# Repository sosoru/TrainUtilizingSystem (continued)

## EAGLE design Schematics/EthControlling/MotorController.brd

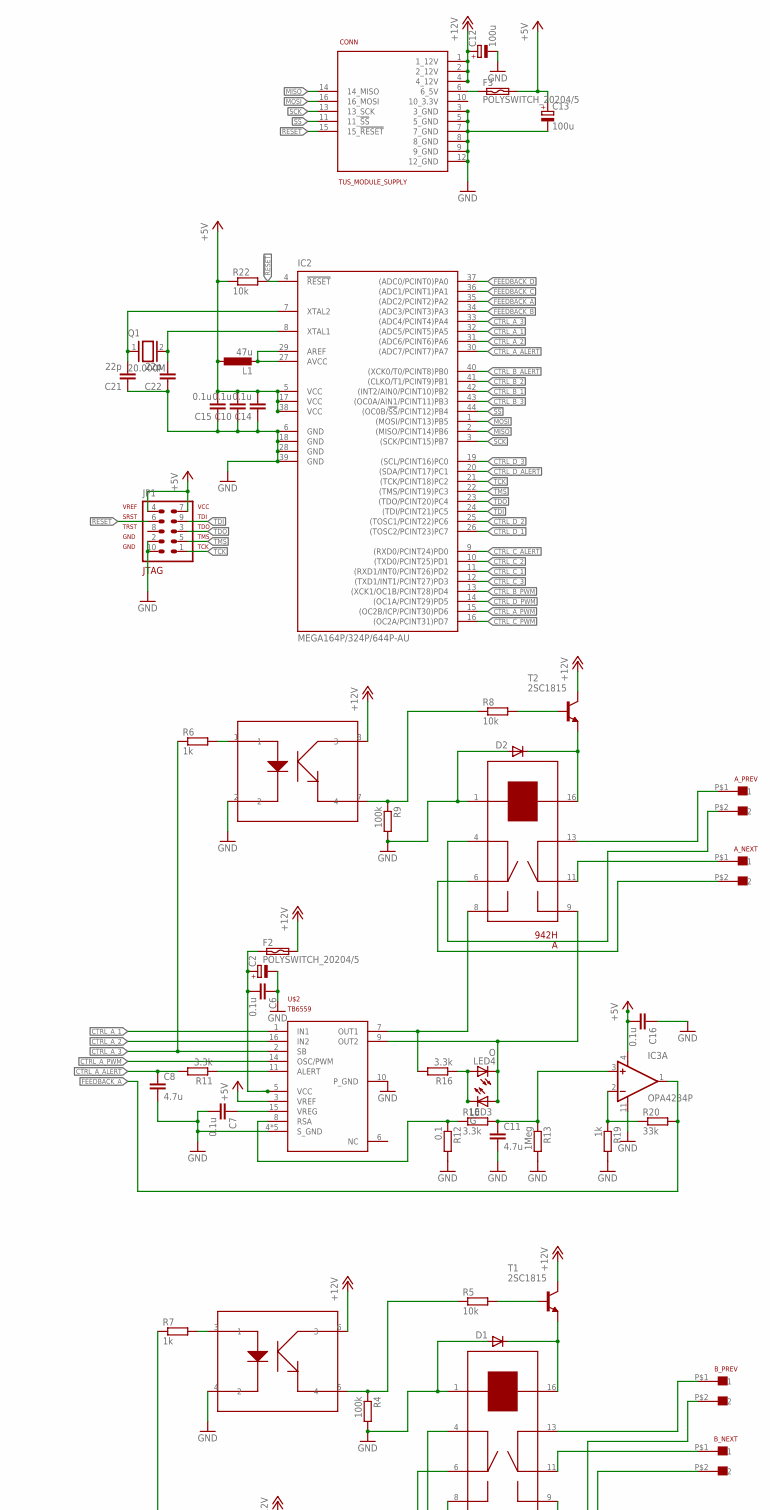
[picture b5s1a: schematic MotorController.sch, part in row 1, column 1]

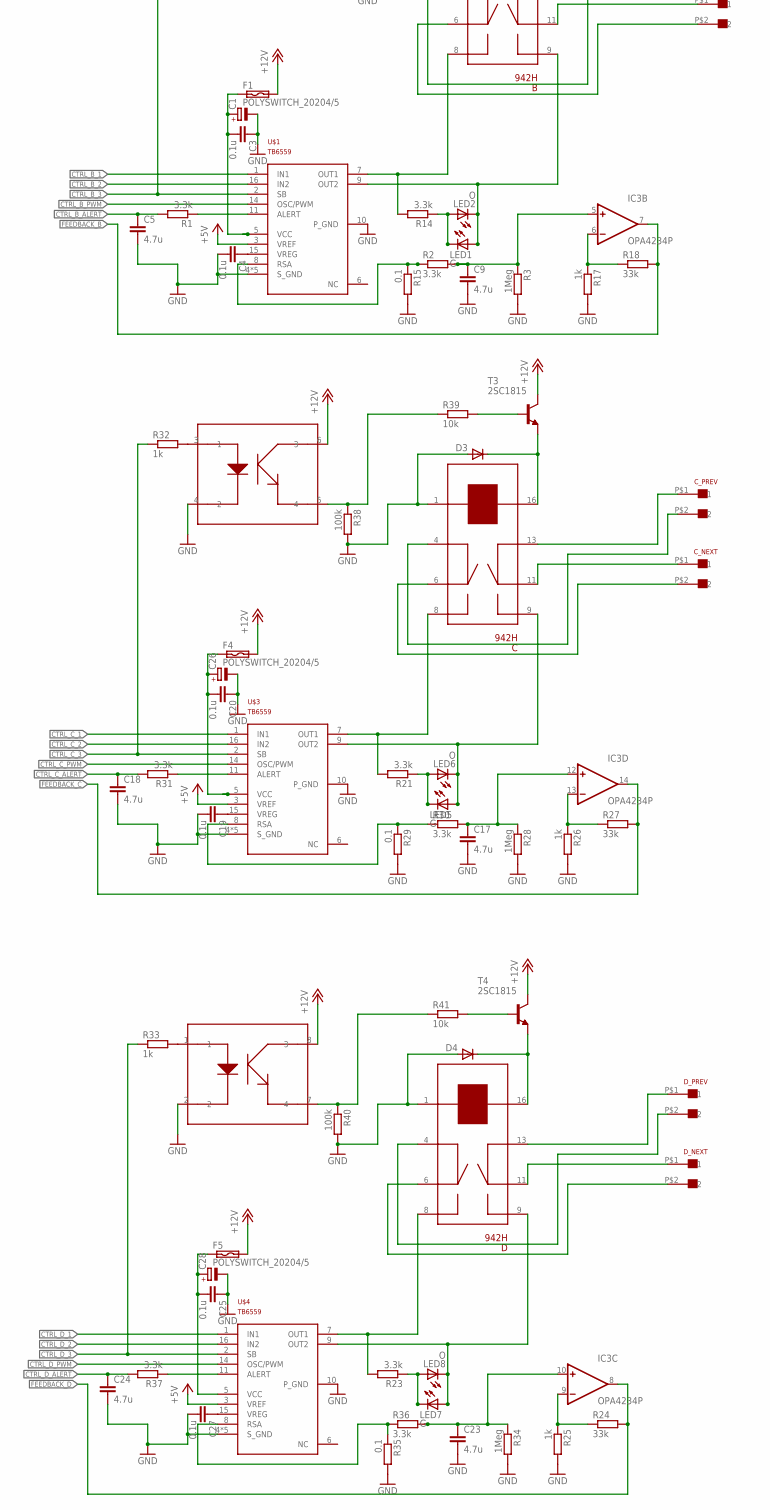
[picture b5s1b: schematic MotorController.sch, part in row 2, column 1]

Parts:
A: 942H; 941H-2C-12D
A_NEXT: XH-2
A_PREV: XH-2
B: 942H; 941H-2C-12D
B_NEXT: XH-2
B_PREV: XH-2
C: 942H; 941H-2C-12D
C1, C2, C26, C28: CPOL-EUE2,5-6E; E2,5-6E
C3, C4, C6, C7, C10, C14, C15, C16, C19, C20, C25, C27: 0.1u; C0603
C5, C8, C9, C11, C17, C18, C23, C24: 4.7u; C0603
C12: 100u; E2,5-6
C13: 100u; E2-5
C21, C22: 22p; C0603
CONN: TUS_MODULE_SUPPLY; 2X08
C_NEXT: XH-2
C_PREV: XH-2
D: 942H; 941H-2C-12D
D1, D2, D3, D4: 1N4148DO35-7; DO35-7
D_NEXT: XH-2
D_PREV: XH-2
F1, F2, F3, F4, F5: POLYSWITCH_20204/5; 0204/5
IC1, IC4: TLP621-2; SOCKET-08
IC2: MEGA164P/324P/644P-AU; TQFP44
IC3: OPA4234P; DIL14
JP1: AVR-JTAG-10
L1: 47u; L3216C
LED1, LED3, LED5, LED7: G; LED3MM
LED2, LED4, LED6, LED8: O; LED3MM
Q1: 20.000M; QS
R1, R2, R10, R11, R14, R16, R21, R23, R30, R31, R36, R37: 3.3k; R0603
R3, R13, R28, R34: 1Meg; R0603
R4, R9, R38, R40: 100k; R0603
R5, R8, R22, R39, R41: 10k; R0603
R6, R7, R17, R19, R25, R26, R32, R33: 1k; R0603
R12, R15, R29, R35: 0.1; R1206
R18, R20, R24, R27: 33k; R0603
T1, T2, T3, T4: 2SC1815; TO92-ECB
U$1, U$2, U$3, U$4: TB6559; HSOP-16

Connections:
!RESET: CONN.15 (15_!RESET), IC2.4 (!RESET), JP1.6, R22.2
!SS: CONN.11 (11_!SS), IC2.44 ((OC0B/!SS!/PCINT12)PB4)
+5V: C10.2, C13.+, C14.2, C15.2, C16.2, F3.2, IC2.5 (VCC), IC2.17 (VCC), IC2.38 (VCC), IC3.4 (V+), JP1.4, JP1.7, L1.1, R22.1, U$1.3 (VREF), U$2.3 (VREF), U$3.3 (VREF), U$4.3 (VREF)
+12V: C12.+, CONN.1 (1_12V), CONN.2 (2_12V), CONN.4 (4_12V), F1.2, F2.2, F4.2, F5.2, IC1.6 (3), IC1.8 (3), IC4.6 (3), IC4.8 (3), T1.C, T2.C, T3.C, T4.C
A_OUT1: A.8 (1), R16.2, U$2.7 (OUT1)
A_OUT2: A.9 ('1), LED3.A, LED4.K (C), U$2.9 (OUT2)
A_OUT3: C.8 (1), R21.2, U$3.7 (OUT1)
A_OUT4: C.9 ('1), LED5.A, LED6.K (C), U$3.9 (OUT2)
A_OUT5: B.8 (1), R14.2, U$1.7 (OUT1)
A_OUT6: B.9 ('1), LED1.A, LED2.K (C), U$1.9 (OUT2)
A_OUT7: D.8 (1), R23.2, U$4.7 (OUT1)
A_OUT8: D.9 ('1), LED7.A, LED8.K (C), U$4.9 (OUT2)
CTRL_A_1: IC2.32 ((ADC5/PCINT5)PA5), U$2.1 (IN1)
CTRL_A_2: IC2.31 ((ADC6/PCINT6)PA6), U$2.16 (IN2)
CTRL_A_3: IC2.33 ((ADC4/PCINT4)PA4), R6.1, U$2.2 (SB)
CTRL_A_ALERT: C8.1, IC2.30 ((ADC7/PCINT7)PA7), R11.2
CTRL_A_PWM: IC2.15 ((OC2B/ICP/PCINT30)PD6), U$2.14 (OSC/PWM)
CTRL_B_1: IC2.42 ((INT2/AIN0/PCINT10)PB2), U$1.1 (IN1)
CTRL_B_2: IC2.41 ((CLKO/T1/PCINT9)PB1), U$1.16 (IN2)
CTRL_B_3: IC2.43 ((OC0A/AIN1/PCINT11)PB3), R7.1, U$1.2 (SB)
CTRL_B_ALERT: C5.1, IC2.40 ((XCK0/T0/PCINT8)PB0), R1.2
CTRL_B_PWM: IC2.13 ((XCK1/OC1B/PCINT28)PD4), U$1.14 (OSC/PWM)
CTRL_C_1: IC2.11 ((RXD1/INT0/PCINT26)PD2), U$3.1 (IN1)
CTRL_C_2: IC2.10 ((TXD0/PCINT25)PD1), U$3.16 (IN2)
CTRL_C_3: IC2.12 ((TXD1/INT1/PCINT27)PD3), R32.1, U$3.2 (SB)
CTRL_C_ALERT: C18.1, IC2.9 ((RXD0/PCINT24)PD0), R31.2
CTRL_C_PWM: IC2.16 ((OC2A/PCINT31)PD7), U$3.14 (OSC/PWM)
CTRL_D_1: IC2.26 ((TOSC2/PCINT23)PC7), U$4.1 (IN1)
CTRL_D_2: IC2.25 ((TOSC1/PCINT22)PC6), U$4.16 (IN2)
CTRL_D_3: IC2.19 ((SCL/PCINT16)PC0), R33.1, U$4.2 (SB)
CTRL_D_ALERT: C24.1, IC2.20 ((SDA/PCINT17)PC1), R37.2
CTRL_D_PWM: IC2.14 ((OC1A/PCINT29)PD5), U$4.14 (OSC/PWM)
D: D.4 (3), D_PREV.P$2 (2)
FEEDBACK_A: IC2.35 ((ADC2/PCINT2)PA2), IC3.1 (OUT), R20.2
FEEDBACK_B: IC2.34 ((ADC3/PCINT3)PA3), IC3.7 (OUT), R18.2
FEEDBACK_C: IC2.36 ((ADC1/PCINT1)PA1), IC3.14 (OUT), R27.2
FEEDBACK_D: IC2.37 ((ADC0/PCINT0)PA0), IC3.8 (OUT), R24.2
GND: A.1 (4), B.1 (4), C.1 (4), C1.-, C2.-, C3.1, C4.2, C5.2, C6.1, C7.2, C8.2, C9.2, C10.1, C11.2, C12.-, C13.-, C14.1, C15.1, C16.1, C17.2, C18.2, C19.2, C20.1, C21.1, C22.1, C23.2, C24.2, C25.1, C26.-, C27.2, C28.-, CONN.3 (3_GND), CONN.5 (5_GND), CONN.7 (7_GND), CONN.8 (8_GND), CONN.9 (9_GND), CONN.12 (12_GND), D.1 (4), D1.A, D2.A, D3.A, D4.A, IC1.2, IC1.4 (2), IC2.6 (GND), IC2.18 (GND), IC2.28 (GND), IC2.39 (GND), IC3.11 (V-), IC4.2, IC4.4 (2), JP1.2, JP1.10, R3.2, R4.2, R9.2, R12.2, R13.2, R15.2, R17.2, R19.2, R25.2, R26.2, R28.2, R29.2, R34.2, R35.2, R38.2, R40.2, U$1.4 (S_GND), U$1.10 (P_GND), U$1.12 (S_GND), U$1.13 (S_GND), U$1.FIN_1 (S_GND), U$1.FIN_2 (S_GND), U$2.4 (S_GND), U$2.10 (P_GND), U$2.12 (S_GND), U$2.13 (S_GND), U$2.FIN_1 (S_GND), U$2.FIN_2 (S_GND), U$3.4 (S_GND), U$3.10 (P_GND), U$3.12 (S_GND), U$3.13 (S_GND), U$3.FIN_1 (S_GND), U$3.FIN_2 (S_GND), U$4.4 (S_GND), U$4.10 (P_GND), U$4.12 (S_GND), U$4.13 (S_GND), U$4.FIN_1 (S_GND), U$4.FIN_2 (S_GND)
MISO: CONN.14 (14_MISO), IC2.2 ((MISO/PCINT14)PB6)
MOSI: CONN.16 (16_MOSI), IC2.1 ((MOSI/PCINT13)PB5)
unnamed: IC2.27 (AVCC), IC2.29 (AREF), L1.2
unnamed: C21.2, IC2.7 (XTAL2), Q1.1
unnamed: C22.2, IC2.8 (XTAL1), Q1.2
unnamed: R11.1, U$2.11 (ALERT)
unnamed: C7.1, U$2.15 (VREG)
unnamed: IC1.1, R6.2
unnamed: IC1.7 (4), R8.1, R9.1
unnamed: LED3.K (C), LED4.A, R16.1
unnamed: C19.1, U$3.15 (VREG)
unnamed: C2.+, C6.2, F2.1, U$2.5 (VCC)
unnamed: IC3.2 (-IN), R19.1, R20.1
unnamed: R31.1, U$3.11 (ALERT)
unnamed: A.6 (2), A_NEXT.P$2 (2)
unnamed: R10.1, R12.1, U$2.8 (RSA)
unnamed: A.11 ('2), A_NEXT.P$1 (1)
unnamed: A.4 (3), A_PREV.P$2 (2)
unnamed: A.13 ('3), A_PREV.P$1 (1)
unnamed: C20.2, C26.+, F4.1, U$3.5 (VCC)
unnamed: LED5.K (C), LED6.A, R21.1
unnamed: IC1.3 (1), R7.2
unnamed: C11.1, IC3.3 (+IN), R10.2, R13.1
unnamed: C.6 (2), C_NEXT.P$2 (2)
unnamed: C.11 ('2), C_NEXT.P$1 (1)
unnamed: C.4 (3), C_PREV.P$2 (2)
unnamed: C.13 ('3), C_PREV.P$1 (1)
unnamed: IC4.5 (4), R38.1, R39.1
unnamed: C.16 ('4), D3.C, T3.E
unnamed: R39.2, T3.B
unnamed: IC3.13 (-IN), R26.1, R27.1
unnamed: C17.1, IC3.12 (+IN), R28.1, R30.2
unnamed: R29.1, R30.1, U$3.8 (RSA)
unnamed: C4.1, U$1.15 (VREG)
unnamed: R1.1, U$1.11 (ALERT)
unnamed: C1.+, C3.2, F1.1, U$1.5 (VCC)
unnamed: LED1.K (C), LED2.A, R14.1
unnamed: IC4.1, R33.2
unnamed: B.6 (2), B_NEXT.P$2 (2)
unnamed: B.11 ('2), B_NEXT.P$1 (1)
unnamed: B.4 (3), B_PREV.P$2 (2)
unnamed: B.13 ('3), B_PREV.P$1 (1)
unnamed: IC1.5 (4), R4.1, R5.1
unnamed: B.16 ('4), D1.C, T1.E
unnamed: R5.2, T1.B
unnamed: IC3.6 (-IN), R17.1, R18.1
unnamed: C9.1, IC3.5 (+IN), R2.2, R3.1
unnamed: R2.1, R15.1, U$1.8 (RSA)
unnamed: C27.1, U$4.15 (VREG)
unnamed: R37.1, U$4.11 (ALERT)
unnamed: C25.2, C28.+, F5.1, U$4.5 (VCC)
unnamed: LED7.K (C), LED8.A, R23.1
unnamed: IC4.3 (1), R32.2
unnamed: D.6 (2), D_NEXT.P$2 (2)
unnamed: D.11 ('2), D_NEXT.P$1 (1)
unnamed: CONN.6 (6_5V), F3.1
unnamed: D.13 ('3), D_PREV.P$1 (1)
unnamed: IC4.7 (4), R40.1, R41.1
unnamed: D.16 ('4), D4.C, T4.E
unnamed: R41.2, T4.B
unnamed: IC3.9 (-IN), R24.1, R25.1
unnamed: C23.1, IC3.10 (+IN), R34.1, R36.2
unnamed: R35.1, R36.1, U$4.8 (RSA)
unnamed: A.16 ('4), D2.C, T2.E
unnamed: R8.2, T2.B
SCK: CONN.13 (13_SCK), IC2.3 ((SCK/PCINT15)PB7)
TCK: IC2.21 ((TCK/PCINT18)PC2), JP1.1
TDI: IC2.24 ((TDI/PCINT21)PC5), JP1.9
TDO: IC2.23 ((TDO/PCINT20)PC4), JP1.3
TMS: IC2.22 ((TMS/PCINT19)PC3), JP1.5

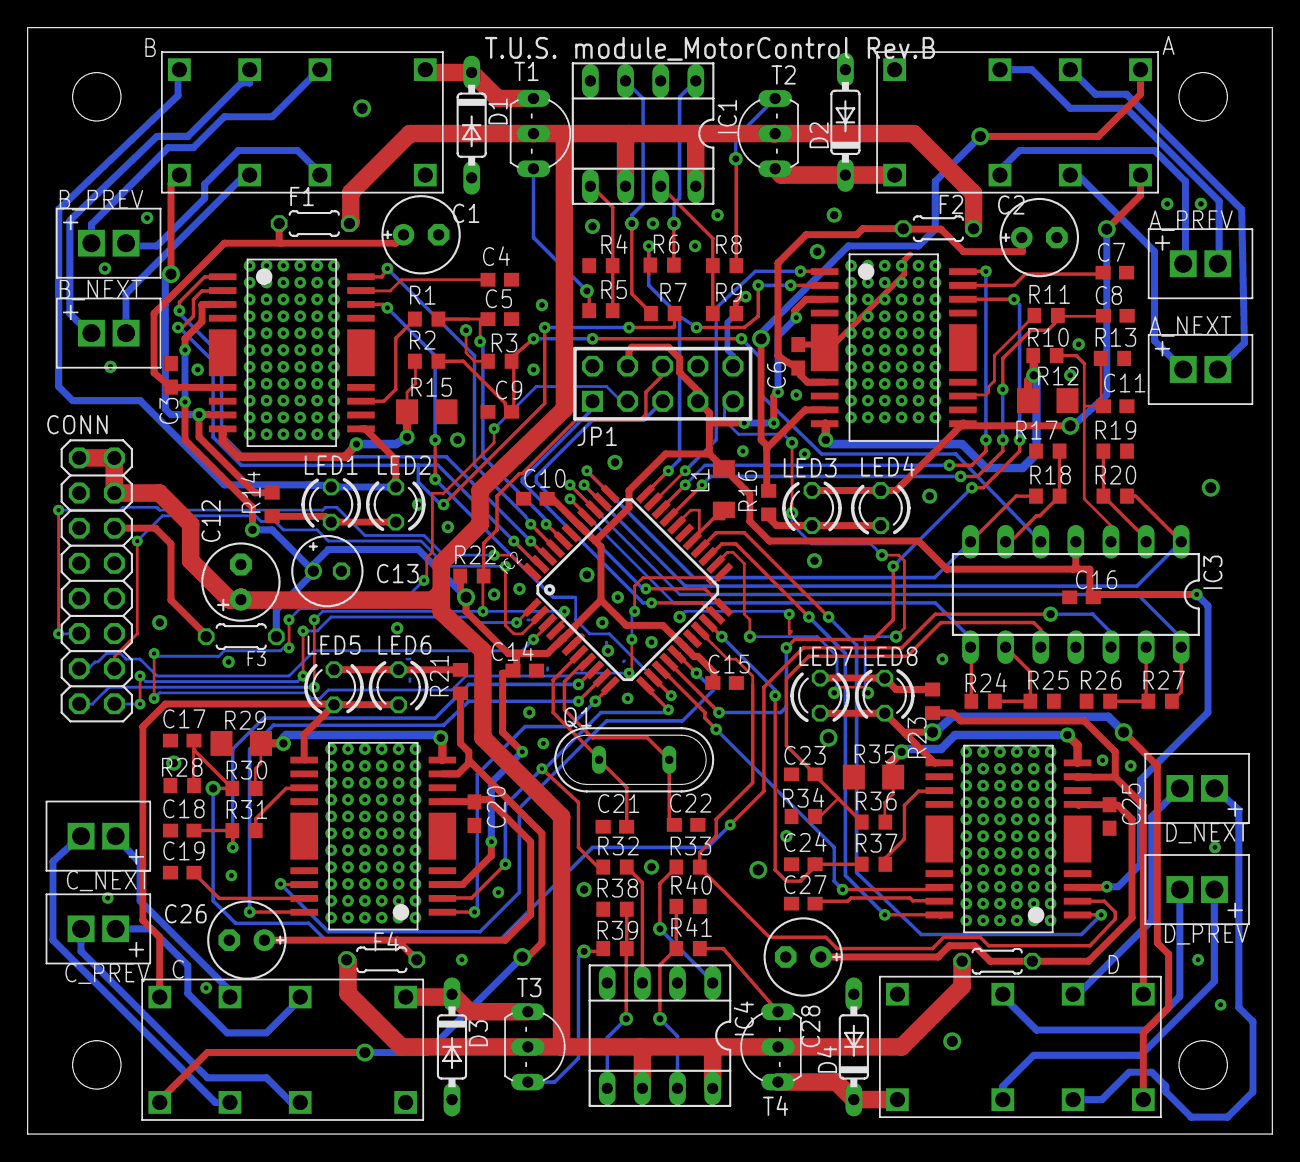
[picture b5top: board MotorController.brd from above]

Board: 2 copper layers, 90.0 x 80.0 mm, 114 parts (0 on the bottom side), 108 nets.

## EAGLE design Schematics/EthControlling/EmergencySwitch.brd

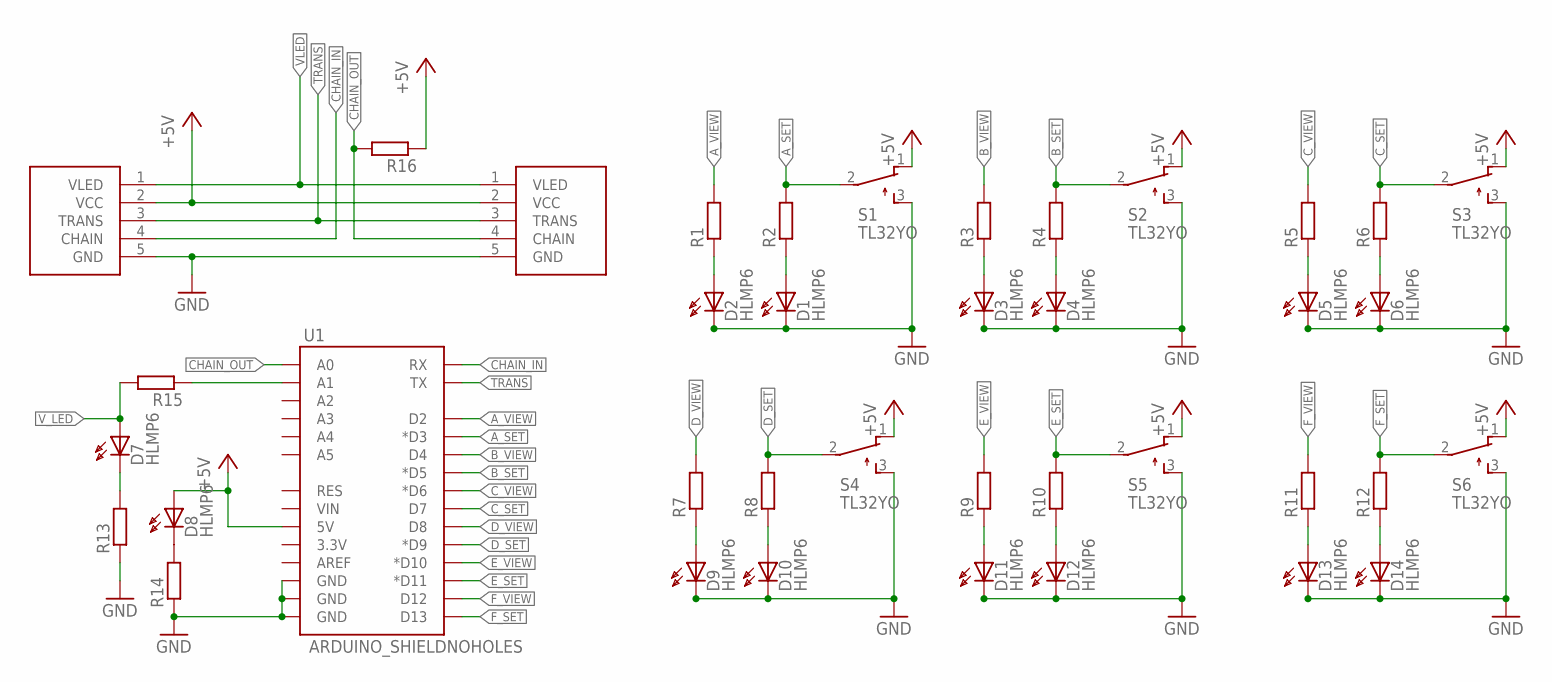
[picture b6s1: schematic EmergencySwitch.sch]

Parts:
CONN_IN: SERIAL_SENSORXH; XH-5
CONN_OUT: SERIAL_SENSORXH; XH-5
D1, D4, D6, D10, D12, D14: HLMP6
D2, D3, D5, D7, D8, D9, D11, D13: HLMP6; MPN HLMP-6500
R1, R2, R3, R4, R5, R6, R7, R8, R9, R10, R11, R12, R13, R14, R15, R16: R-EU_R0603; R0603
S1, S2, S3, S4, S5, S6: TL32YO; TL3XYO
U1: ARDUINO_SHIELDNOHOLES; DUEMILANOVE_SHIELD_NOHOLES

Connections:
+5V: CONN_IN.2 (VCC), CONN_OUT.2 (VCC), D8.A, R16.1, S1.1 (O), S2.1 (O), S3.1 (O), S4.1 (O), S5.1 (O), S6.1 (O), U1.5V
A_SET: R2.2, S1.2, U1.D3 (*D3)
A_VIEW: R1.2, U1.D2
B_SET: R4.2, S2.2, U1.D5 (*D5)
B_VIEW: R3.2, U1.D4
CHAIN_IN: CONN_IN.4 (CHAIN), U1.RX
CHAIN_OUT: CONN_OUT.4 (CHAIN), R16.2, U1.A0
C_SET: R6.2, S3.2, U1.D7
C_VIEW: R5.2, U1.D6 (*D6)
D_SET: R8.2, S4.2, U1.D9 (*D9)
D_VIEW: R7.2, U1.D8
E_SET: R10.2, S5.2, U1.D11 (*D11)
E_VIEW: R9.2, U1.D10 (*D10)
F_SET: R12.2, S6.2, U1.D13
F_VIEW: R11.2, U1.D12
GND: CONN_IN.5 (GND), CONN_OUT.5 (GND), D1.K, D2.K, D3.K, D4.K, D5.K, D6.K, D9.K, D10.K, D11.K, D12.K, D13.K, D14.K, R13.1, R14.1, S1.3 (S), S2.3 (S), S3.3 (S), S4.3 (S), S5.3 (S), S6.3 (S), U1.GND@0 (GND), U1.GND@1 (GND), U1.GND@2 (GND)
unnamed: D7.K, R13.2
unnamed: D8.K, R14.2
unnamed: D1.A, R2.1
unnamed: D4.A, R4.1
unnamed: D3.A, R3.1
unnamed: D6.A, R6.1
unnamed: D2.A, R1.1
unnamed: D5.A, R5.1
unnamed: D10.A, R8.1
unnamed: D9.A, R7.1
unnamed: D12.A, R10.1
unnamed: D11.A, R9.1
unnamed: D14.A, R12.1
unnamed: D13.A, R11.1
unnamed: R15.1, U1.A1
TRANS: CONN_IN.3 (TRANS), CONN_OUT.3 (TRANS), U1.TX
VLED: CONN_IN.1 (VLED), CONN_OUT.1 (VLED)
V_LED: D7.A, R15.2

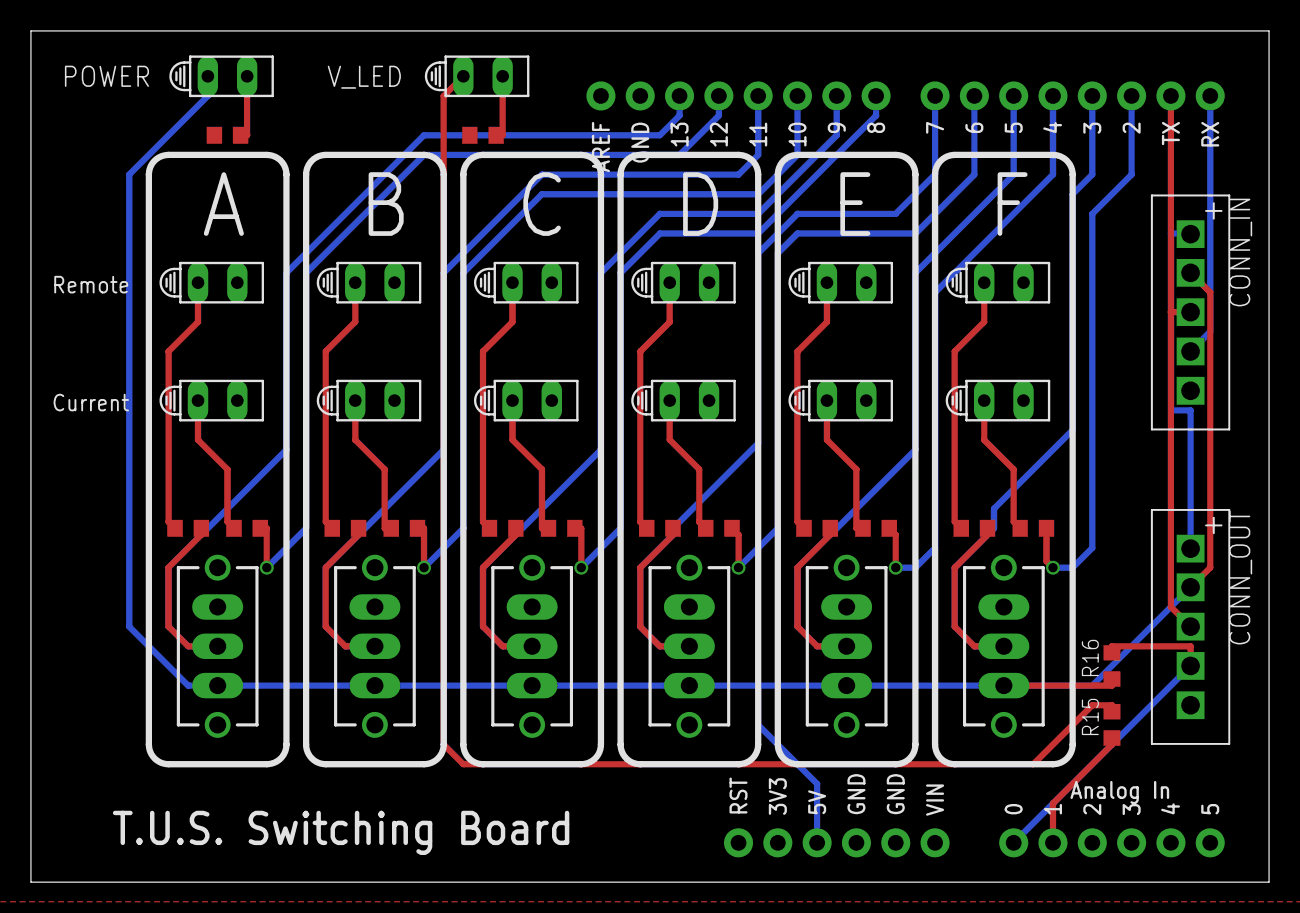
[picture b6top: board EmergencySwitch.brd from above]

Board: 2 copper layers, 80.0 x 55.0 mm, 39 parts (0 on the bottom side), 34 nets.

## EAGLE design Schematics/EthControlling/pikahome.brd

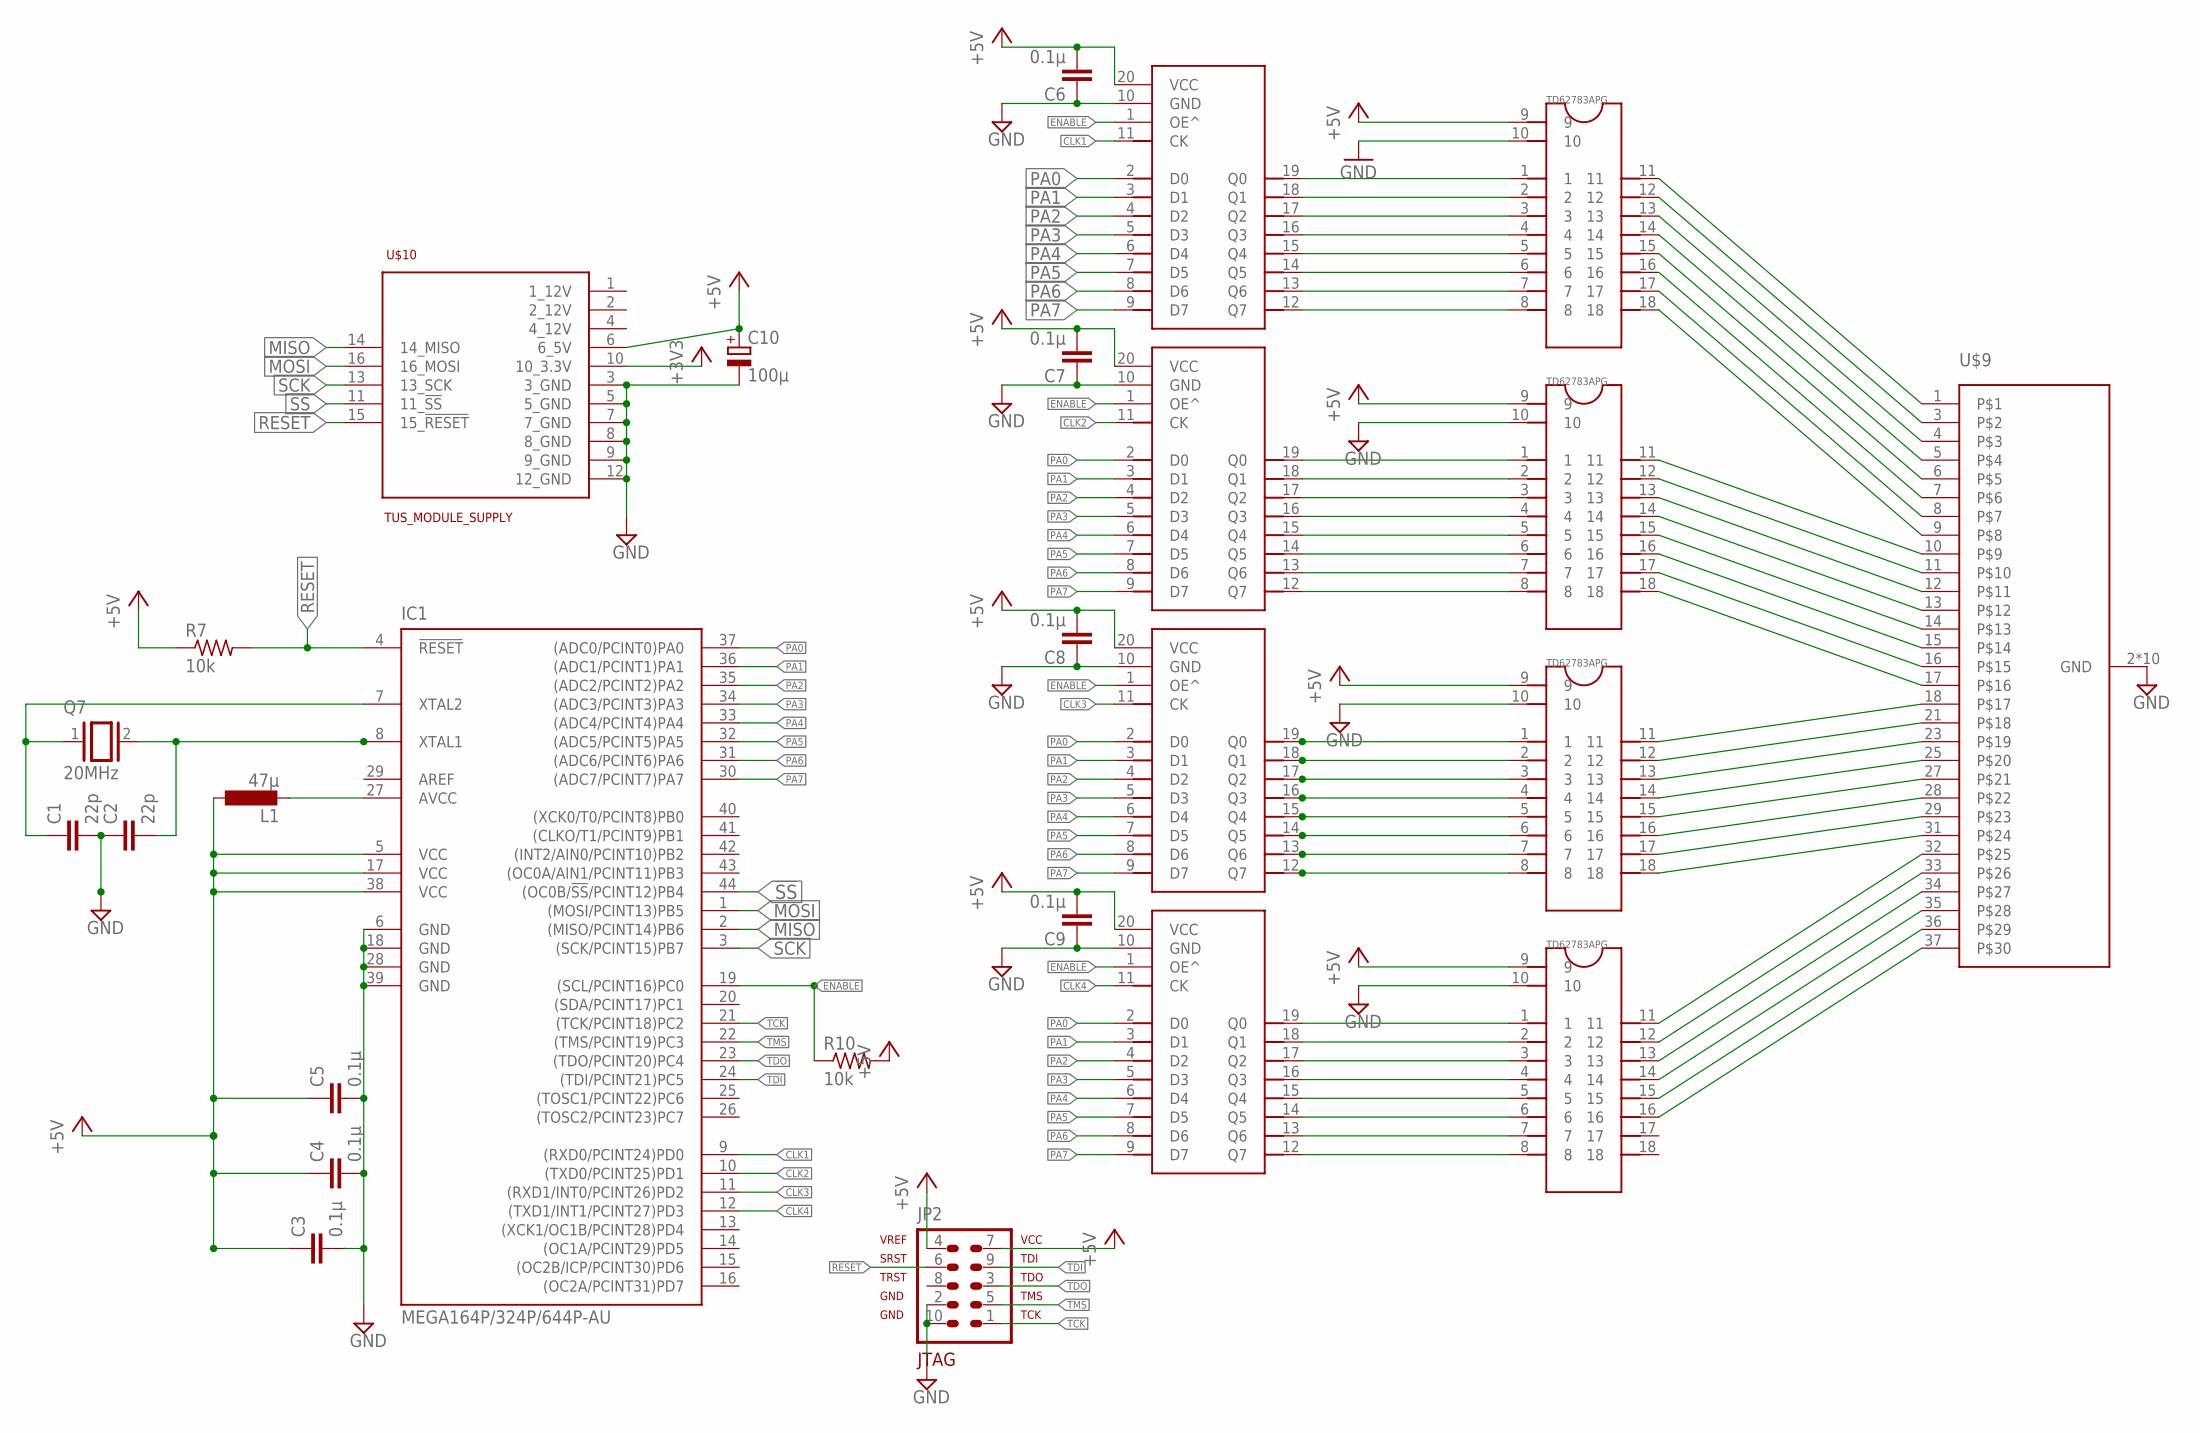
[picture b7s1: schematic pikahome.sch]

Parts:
C1, C2: 22p; C0603
C3, C4, C5, C6, C7, C8, C9: 0.1μ; C0603
C10: 100μ; TT2D5
IC1: MEGA164P/324P/644P-AU; TQFP44
JP2: AVR-JTAG-10
L1: 47μ; L3216C
Q7: 20MHz; QS
R7, R10: 10k; R0603
U$1, U$2, U$6, U$8: TD62783APG; DIL18
U$3, U$4, U$5, U$7: 74VHC574F; SO20W
U$9: LED_40; PAK100/2500-40
U$10: TUS_MODULE_SUPPLY; 2X08

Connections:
!SS: IC1.44 ((OC0B/!SS!/PCINT12)PB4), U$10.11 (11_!SS)
+3V3: U$10.10 (10_3.3V)
+5V: C3.1, C4.1, C5.1, C6.2, C7.2, C8.2, C9.2, C10.+, IC1.5 (VCC), IC1.17 (VCC), IC1.38 (VCC), JP2.4, JP2.7, L1.1, R7.1, R10.2, U$1.9, U$2.9, U$3.20 (VCC), U$4.20 (VCC), U$5.20 (VCC), U$6.9, U$7.20 (VCC), U$8.9, U$10.6 (6_5V)
AREF: IC1.29 (AREF)
AVCC: IC1.27 (AVCC), L1.2
CLK1: IC1.9 ((RXD0/PCINT24)PD0), U$3.11 (CK)
CLK2: IC1.10 ((TXD0/PCINT25)PD1), U$4.11 (CK)
CLK3: IC1.11 ((RXD1/INT0/PCINT26)PD2), U$5.11 (CK)
CLK4: IC1.12 ((TXD1/INT1/PCINT27)PD3), U$7.11 (CK)
ENABLE: IC1.19 ((SCL/PCINT16)PC0), R10.1, U$3.1 (OE^), U$4.1 (OE^), U$5.1 (OE^), U$7.1 (OE^)
GND: C1.2, C2.1, C3.2, C4.2, C5.2, C6.1, C7.1, C8.1, C9.1, C10.-, IC1.6 (GND), IC1.18 (GND), IC1.28 (GND), IC1.39 (GND), JP2.2, JP2.10, U$1.10, U$2.10, U$3.10 (GND), U$4.10 (GND), U$5.10 (GND), U$6.10, U$7.10 (GND), U$8.10, U$9.2 (GND), U$9.19 (GND), U$9.20 (GND), U$9.22 (GND), U$9.24 (GND), U$9.26 (GND), U$9.30 (GND), U$9.38 (GND), U$9.39 (GND), U$9.40 (GND), U$10.3 (3_GND), U$10.5 (5_GND), U$10.7 (7_GND), U$10.8 (8_GND), U$10.9 (9_GND), U$10.12 (12_GND)
MISO: IC1.2 ((MISO/PCINT14)PB6), U$10.14 (14_MISO)
MOSI: IC1.1 ((MOSI/PCINT13)PB5), U$10.16 (16_MOSI)
unnamed: U$1.1, U$3.19 (Q0)
unnamed: U$1.2, U$3.18 (Q1)
unnamed: U$7.19 (Q0), U$8.1
unnamed: U$1.3, U$3.17 (Q2)
unnamed: U$1.4, U$3.16 (Q3)
unnamed: U$2.8, U$4.12 (Q7)
unnamed: U$7.18 (Q1), U$8.2
unnamed: U$7.17 (Q2), U$8.3
unnamed: U$1.5, U$3.15 (Q4)
unnamed: C1.1, IC1.7 (XTAL2), Q7.1
unnamed: C2.2, IC1.8 (XTAL1), Q7.2
unnamed: U$1.6, U$3.14 (Q5)
unnamed: U$1.7, U$3.13 (Q6)
unnamed: U$2.1, U$4.19 (Q0)
unnamed: U$5.19 (Q0), U$6.1
unnamed: U$1.8, U$3.12 (Q7)
unnamed: U$7.16 (Q3), U$8.4
unnamed: U$7.15 (Q4), U$8.5
unnamed: U$2.2, U$4.18 (Q1)
unnamed: U$5.18 (Q1), U$6.2
unnamed: U$5.17 (Q2), U$6.3
unnamed: U$2.3, U$4.17 (Q2)
unnamed: U$2.4, U$4.16 (Q3)
unnamed: U$5.16 (Q3), U$6.4
unnamed: U$5.15 (Q4), U$6.5
unnamed: U$5.14 (Q5), U$6.6
unnamed: U$5.13 (Q6), U$6.7
unnamed: U$5.12 (Q7), U$6.8
unnamed: U$2.5, U$4.15 (Q4)
unnamed: U$2.6, U$4.14 (Q5)
unnamed: U$2.7, U$4.13 (Q6)
unnamed: U$7.14 (Q5), U$8.6
unnamed: U$7.13 (Q6), U$8.7
unnamed: U$7.12 (Q7), U$8.8
unnamed: U$1.11, U$9.1
unnamed: U$1.12, U$9.3
unnamed: U$1.13, U$9.4
unnamed: U$1.14, U$9.5
unnamed: U$1.15, U$9.6
unnamed: U$1.16, U$9.7
unnamed: U$1.17, U$9.8
unnamed: U$1.18, U$9.9
unnamed: U$2.11, U$9.10
unnamed: U$2.12, U$9.11
unnamed: U$2.13, U$9.12
unnamed: U$2.14, U$9.13
unnamed: U$2.15, U$9.14
unnamed: U$2.16, U$9.15
unnamed: U$2.17, U$9.16
unnamed: U$2.18, U$9.17
unnamed: U$6.11, U$9.18
unnamed: U$6.12, U$9.21
unnamed: U$6.13, U$9.23
unnamed: U$6.14, U$9.25
unnamed: U$6.15, U$9.27
unnamed: U$6.16, U$9.28
unnamed: U$6.17, U$9.29
unnamed: U$6.18, U$9.31
unnamed: U$8.11, U$9.32
unnamed: U$8.12, U$9.33
unnamed: U$8.13, U$9.34
unnamed: U$8.14, U$9.35
unnamed: U$8.15, U$9.36
unnamed: U$8.16, U$9.37
PA0: IC1.37 ((ADC0/PCINT0)PA0), U$3.2 (D0), U$4.2 (D0), U$5.2 (D0), U$7.2 (D0)
PA1: IC1.36 ((ADC1/PCINT1)PA1), U$3.3 (D1), U$4.3 (D1), U$5.3 (D1), U$7.3 (D1)
PA2: IC1.35 ((ADC2/PCINT2)PA2), U$3.4 (D2), U$4.4 (D2), U$5.4 (D2), U$7.4 (D2)
PA3: IC1.34 ((ADC3/PCINT3)PA3), U$3.5 (D3), U$4.5 (D3), U$5.5 (D3), U$7.5 (D3)
PA4: IC1.33 ((ADC4/PCINT4)PA4), U$3.6 (D4), U$4.6 (D4), U$5.6 (D4), U$7.6 (D4)
PA5: IC1.32 ((ADC5/PCINT5)PA5), U$3.7 (D5), U$4.7 (D5), U$5.7 (D5), U$7.7 (D5)
PA6: IC1.31 ((ADC6/PCINT6)PA6), U$3.8 (D6), U$4.8 (D6), U$5.8 (D6), U$7.8 (D6)
PA7: IC1.30 ((ADC7/PCINT7)PA7), U$3.9 (D7), U$4.9 (D7), U$5.9 (D7), U$7.9 (D7)
RESET: IC1.4 (!RESET), JP2.6, R7.2, U$10.15 (15_!RESET)
SCK: IC1.3 ((SCK/PCINT15)PB7), U$10.13 (13_SCK)
TCK: IC1.21 ((TCK/PCINT18)PC2), JP2.1
TDI: IC1.24 ((TDI/PCINT21)PC5), JP2.9
TDO: IC1.23 ((TDO/PCINT20)PC4), JP2.3
TMS: IC1.22 ((TMS/PCINT19)PC3), JP2.5

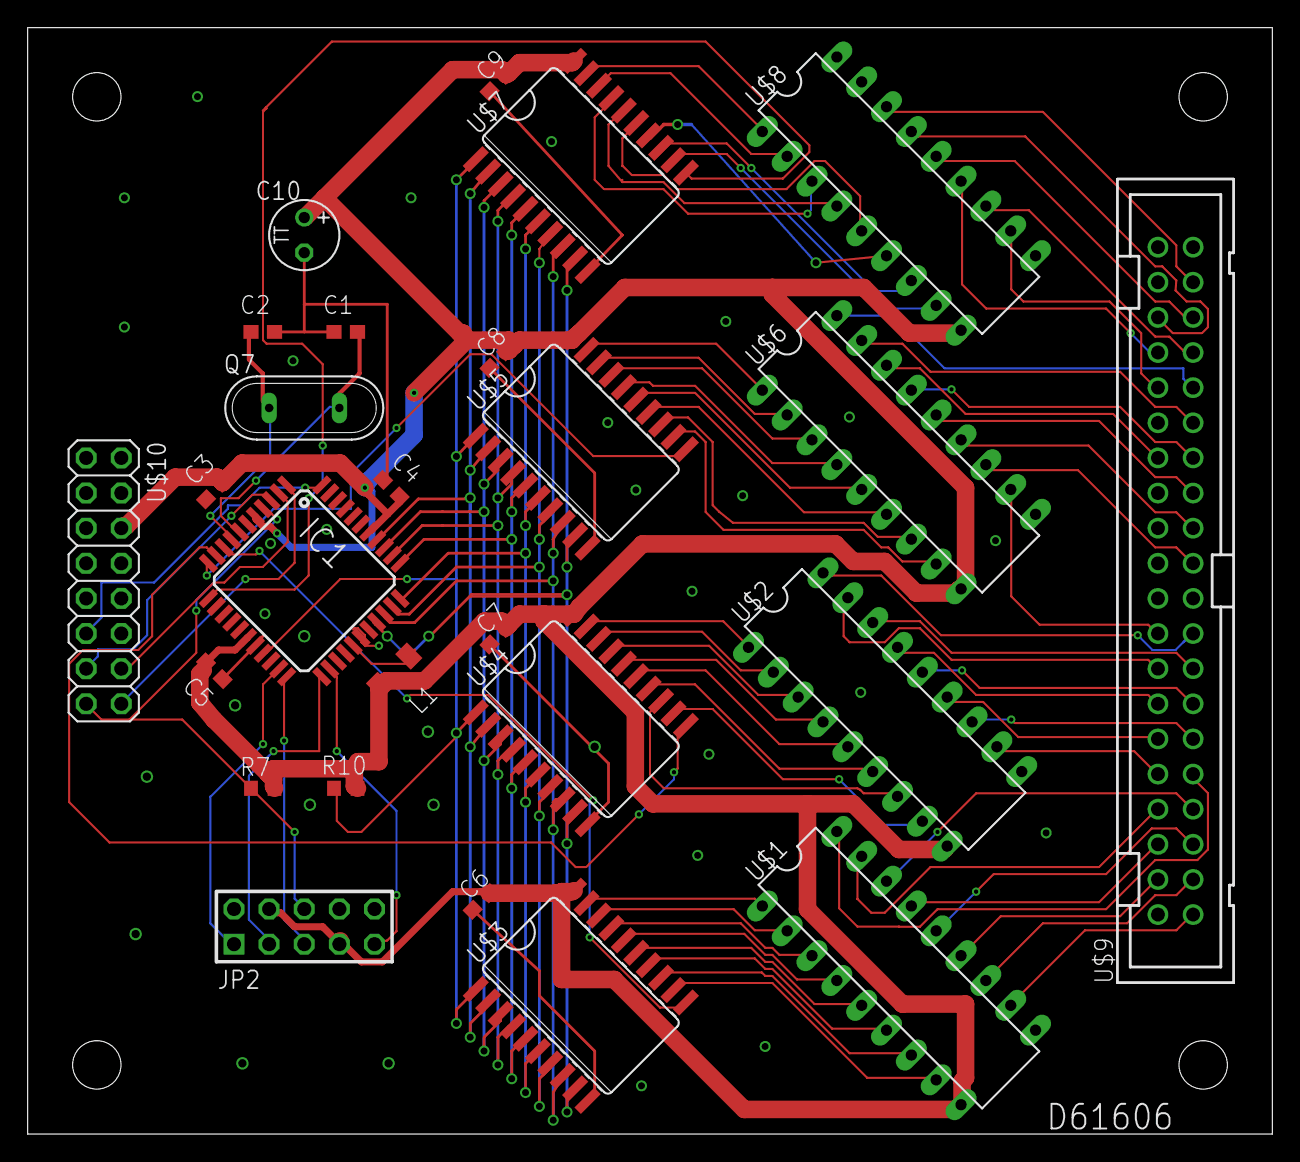
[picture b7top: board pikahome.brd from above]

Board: 2 copper layers, 90.0 x 80.0 mm, 26 parts (0 on the bottom side), 89 nets.
